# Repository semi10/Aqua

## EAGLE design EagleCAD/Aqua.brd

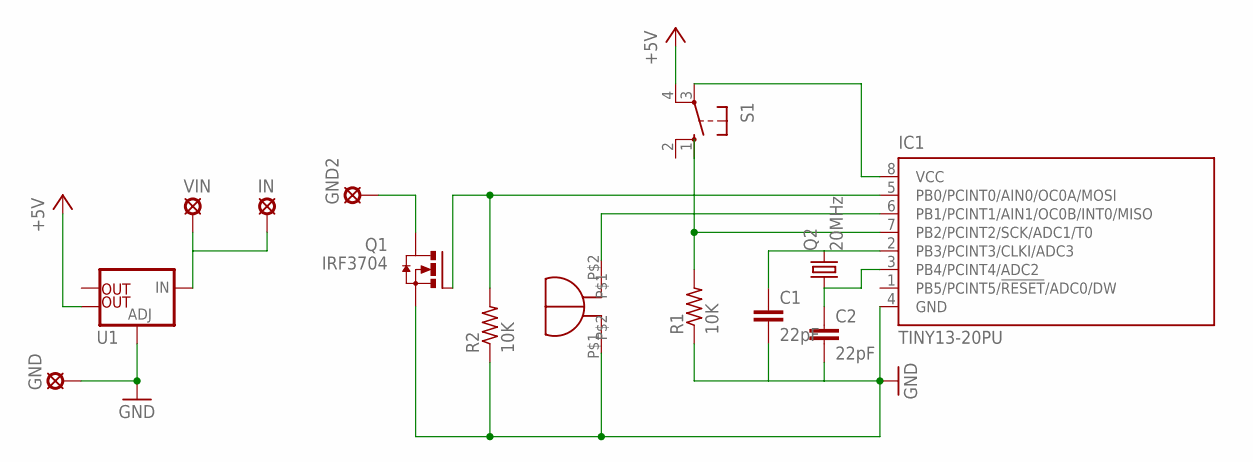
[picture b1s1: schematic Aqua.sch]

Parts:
C1, C2: 22pF; C5B2.5
GND, GND2: LSP11
IC1: TINY13-20PU; DIL08
IN: LSP11
Q1: IRF3704; TO220AH
Q2: 20MHz; HC49U-V
R1, R2: 10K; 0207/10
S1: 10-XX; B3F-10XX
U1: V_REG_LM1117SOT223; SOT223
U$1: COMPUTER_BUZZERCOMPUTER_BUZZER; DGGDG
VIN: LSP11

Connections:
+5V: S1.4 (P1), U1.4 (OUT)
GND: C1.2, C2.2, GND.MP, IC1.4 (GND), Q1.E (S), R1.1, R2.1, U1.1 (ADJ), U$1.P$1
unnamed: GND2.MP, Q1.C (D)
unnamed: IC1.6 (PB1/PCINT1/AIN1/OC0B/INT0/MISO), U$1.P$2
unnamed: C1.1, IC1.2 (PB3/PCINT3/CLKI/ADC3), Q2.2
unnamed: IC1.7 (PB2/PCINT2/SCK/ADC1/T0), R1.2, S1.1 (S)
unnamed: IC1.5 (PB0/PCINT0/AIN0/OC0A/MOSI), Q1.B (G), R2.2
unnamed: C2.1, IC1.3 (PB4/PCINT4/ADC2), Q2.1
unnamed: IC1.8 (VCC), S1.3
unnamed: IN.MP, U1.3 (IN), VIN.MP

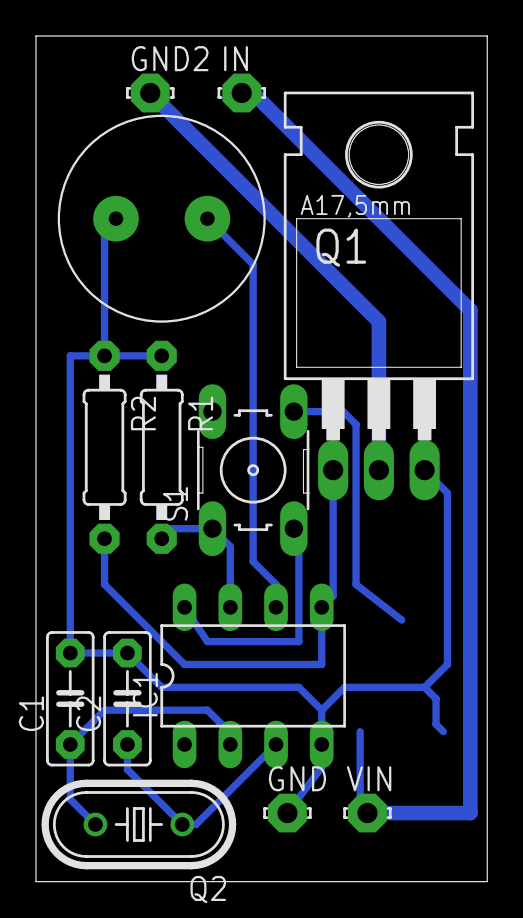
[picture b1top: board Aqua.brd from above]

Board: 2 copper layers, 25.1 x 47.0 mm, 14 parts (1 on the bottom side), 10 nets.

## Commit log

2015-06-01 Created
2015-07-16 Just Created
2015-07-24 Time count improvement
2015-11-26 Timing changed

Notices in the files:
parts and their libraries:
SparkFun-PowerIC: Licensing: Creative Commons ShareAlike 4.0 International - https://creativecommons.org/licenses/by-sa/4.0
